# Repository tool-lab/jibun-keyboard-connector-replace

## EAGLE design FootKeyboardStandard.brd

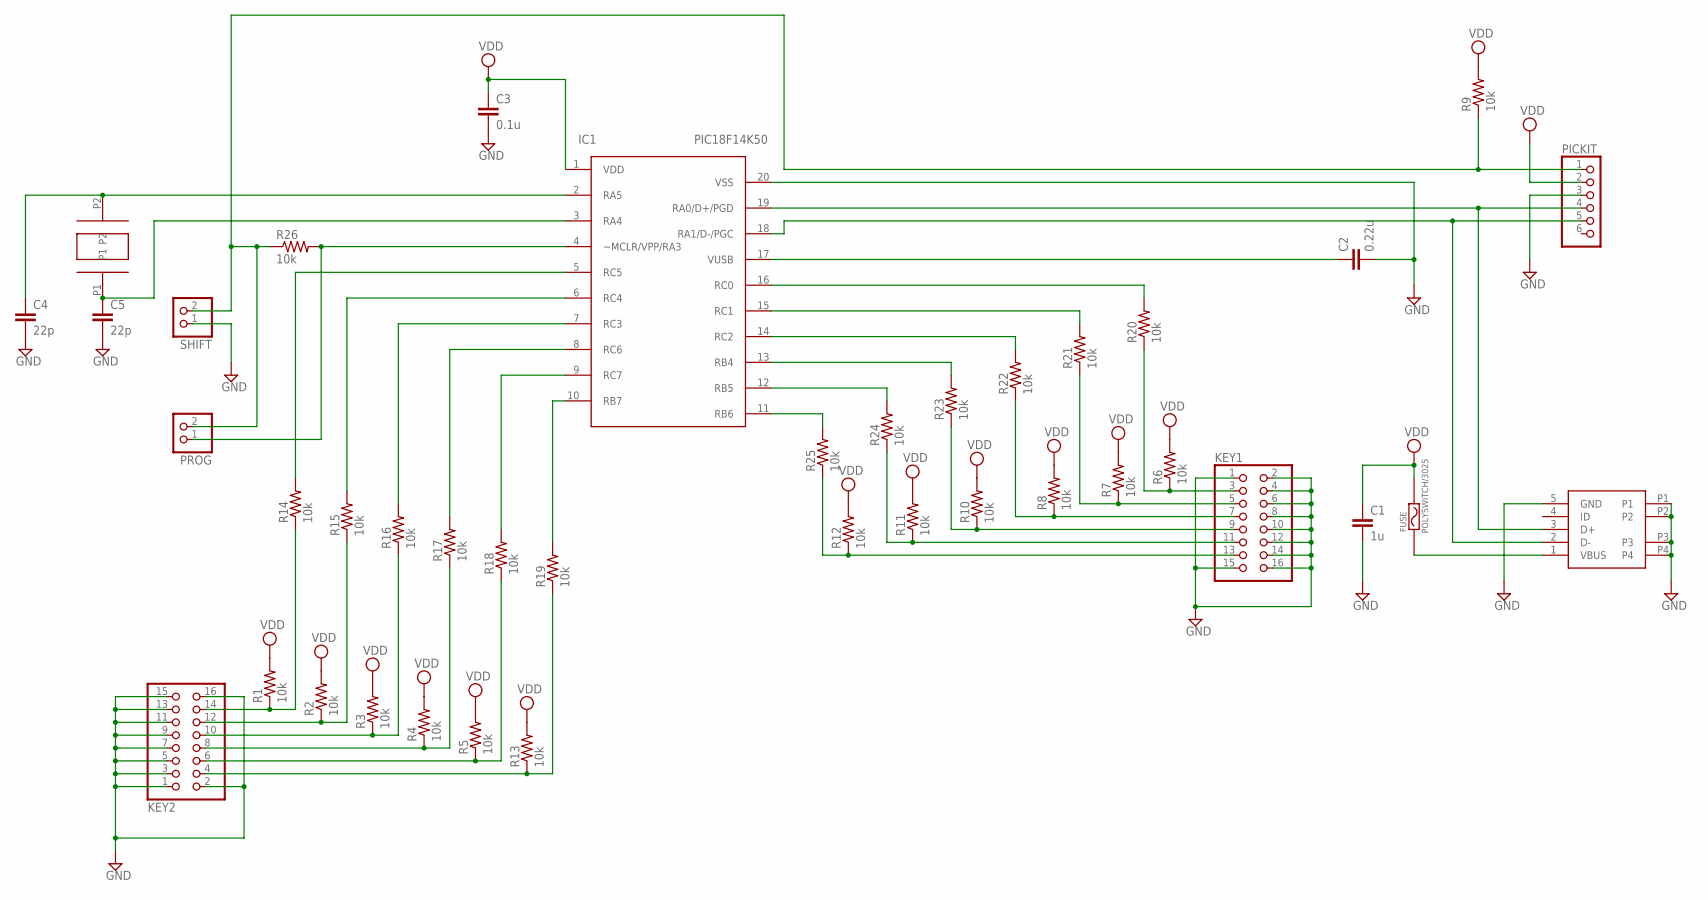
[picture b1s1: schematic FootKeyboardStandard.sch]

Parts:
C1: 1u; C025-025X050
C2: 0.22u; C025-025X050
C3: 0.1u; C025-025X050
C4, C5: 22p; C025-025X050
FUSE: POLYSWITCH/3025; SMD/30X25
IC1: PIC18F14K50; DIL20
KEY1, KEY2: PINHD-2X8; 2X08
PICKIT: PINHD-1X6; 1X06
PROG: PINHD-1X2; 1X02
R1, R2, R3, R4, R5, R6, R7, R8, R9, R10, R11, R12, R13, R14, R15, R16, R17, R18, R19, R20, R21, R22, R23, R24, R25, R26: 10k; 0204/7
SHIFT: PINHD-1X2; 1X02
USB: AKIZUKI-USB-MINI-B
XTAL: 12M; AKIZUKI-XTAL

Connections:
GND: C1.2, C2.2, C3.2, C4.2, C5.2, IC1.20 (VSS), KEY1.1, KEY1.2, KEY1.4, KEY1.6, KEY1.8, KEY1.10, KEY1.12, KEY1.14, KEY1.15, KEY1.16, KEY2.1, KEY2.2, KEY2.3, KEY2.5, KEY2.7, KEY2.9, KEY2.11, KEY2.13, KEY2.15, KEY2.16, PICKIT.3, SHIFT.1, USB.5 (GND), USB.P1, USB.P2, USB.P3, USB.P4
unnamed: IC1.19 (RA0/D+/PGD), PICKIT.4, USB.3 (D+)
unnamed: C5.1, IC1.3 (RA4), XTAL.P1
unnamed: C4.1, IC1.2 (RA5), XTAL.P2
unnamed: IC1.18 (RA1/D-/PGC), PICKIT.5, USB.2 (D-)
unnamed: IC1.10 (RB7), R19.2
unnamed: FUSE.P1, USB.1 (VBUS)
unnamed: IC1.9 (RC7), R18.2
unnamed: C2.1, IC1.17 (VUSB)
unnamed: KEY2.10, R3.1, R16.1
unnamed: KEY2.8, R4.1, R17.1
unnamed: KEY2.6, R5.1, R18.1
unnamed: KEY2.4, R13.1, R19.1
unnamed: KEY2.14, R1.1, R14.1
unnamed: KEY2.12, R2.1, R15.1
unnamed: IC1.8 (RC6), R17.2
unnamed: IC1.16 (RC0), R20.2
unnamed: IC1.15 (RC1), R21.2
unnamed: IC1.14 (RC2), R22.2
unnamed: KEY1.9, R10.1, R23.1
unnamed: KEY1.11, R11.1, R24.1
unnamed: KEY1.13, R12.1, R25.1
unnamed: IC1.7 (RC3), R16.2
unnamed: IC1.6 (RC4), R15.2
unnamed: IC1.5 (RC5), R14.2
unnamed: KEY1.3, R6.1, R20.1
unnamed: KEY1.5, R7.1, R21.1
unnamed: KEY1.7, R8.1, R22.1
unnamed: IC1.13 (RB4), R23.2
unnamed: IC1.12 (RB5), R24.2
unnamed: IC1.11 (RB6), R25.2
unnamed: PICKIT.1, PROG.2, R9.1, R26.1, SHIFT.2
unnamed: IC1.4 (~MCLR/VPP/RA3), PROG.1, R26.2
VDD: C1.1, C3.1, FUSE.P2, IC1.1 (VDD), PICKIT.2, R1.2, R2.2, R3.2, R4.2, R5.2, R6.2, R7.2, R8.2, R9.2, R10.2, R11.2, R12.2, R13.2

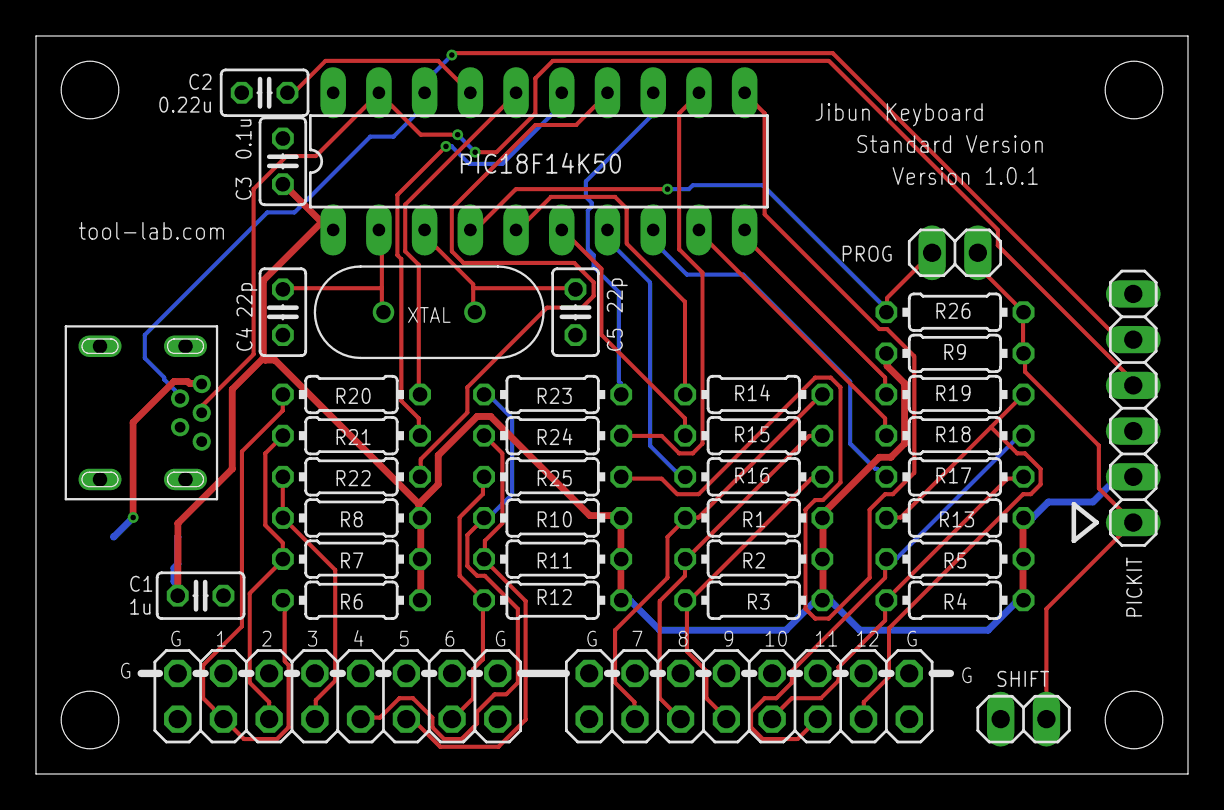
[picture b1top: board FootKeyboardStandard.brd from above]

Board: 2 copper layers, 64.0 x 41.0 mm, 40 parts (1 on the bottom side), 34 nets.
